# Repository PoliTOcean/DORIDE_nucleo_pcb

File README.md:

# NOME_REPO

> **Hai appena creato la repo da questo template? Fai questi passi, poi cancella questo riquadro.**
>
> 1. Rinomina la repo nel formato `<rov>_<componente>_pcb` (es. `nereo_power_pcb`).
> 2. Aggiungi il topic **`electronics`** (ingranaggio accanto ad "About"). I topic non vengono copiati dal template.
> 3. *Settings → Pages → Deploy from a branch → main → /docs → Save*.
> 4. Metti il progetto KiCad dentro `hardware/` (un solo `.kicad_pro`), con le librerie della scheda in `hardware/lib/local/`.
> 5. Sostituisci `NOME_REPO`, `NOME_PROGETTO` e il link al firmware qui sotto. `NOME_PROGETTO` è il nome del file `.kicad_pro` senza estensione.
> 6. Fai `git pull` prima di ogni modifica: dopo ogni push il bot aggiunge i render.

Descrizione della scheda (ROV, funzione, microcontrollore, numero di layer).
Firmware: [NOME_REPO_FIRMWARE](https://github.com/PoliTOcean/NOME_REPO_FIRMWARE)

| Top | Bottom |
|---|---|
|  |  |

## File di produzione

Gerber, forature e PDF dello schema si scaricano da **Actions → ultima run → pcb-outputs**.

## Struttura

~~~
hardware/            progetto KiCad
hardware/lib/local/  simboli, footprint e modelli 3D usati solo da questa scheda
docs/                render e interactive BOM (generati dal bot, non modificare)
~~~

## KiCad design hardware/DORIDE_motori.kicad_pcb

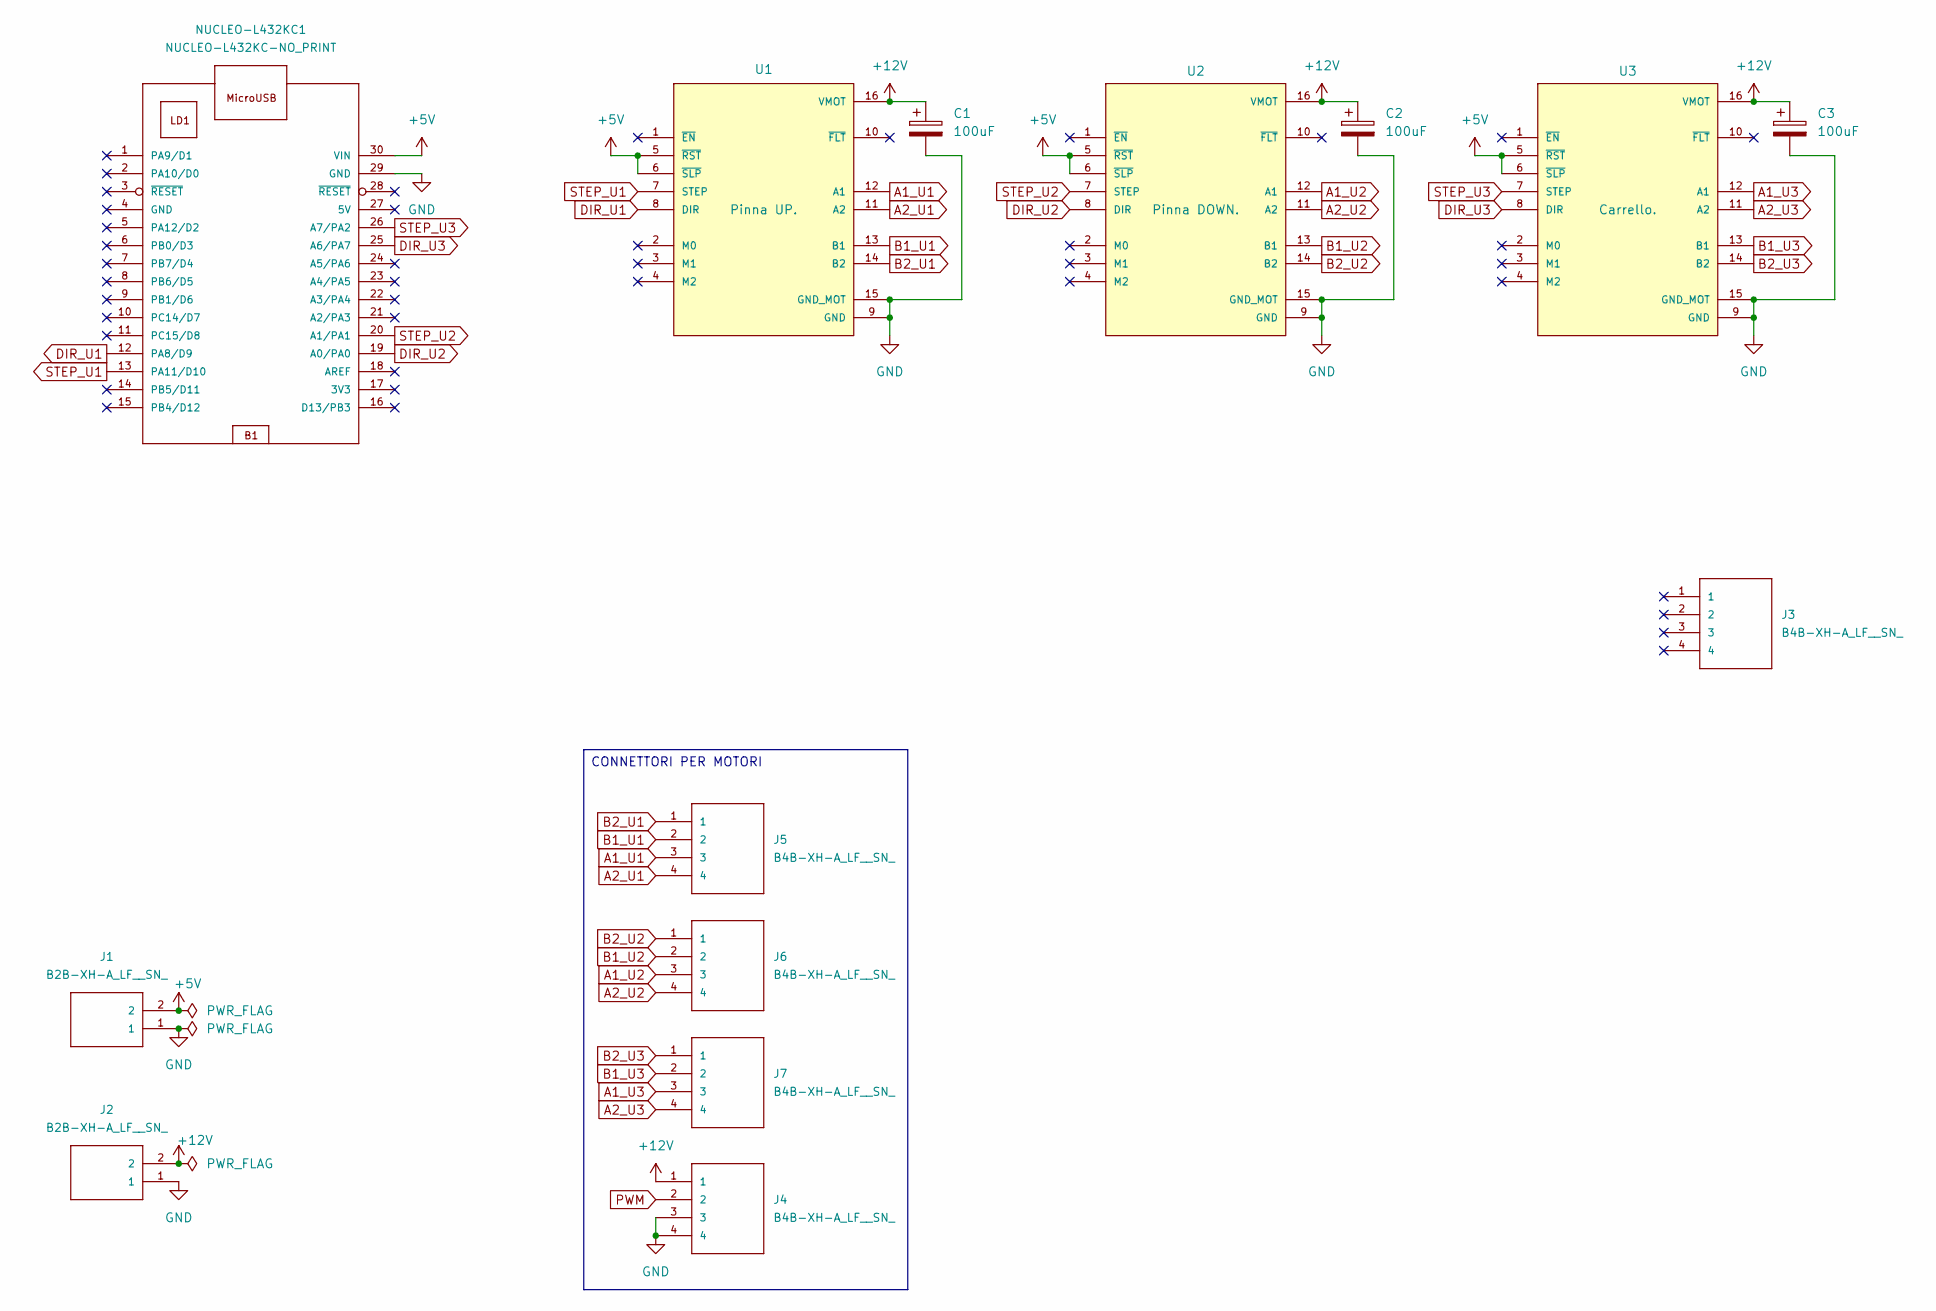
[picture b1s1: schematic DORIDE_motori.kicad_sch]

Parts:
C1, C2, C3: 100uF; CP_Elec_6.3x5.4
J1, J2: B2B-XH-A_LF__SN_; SHDR2W64P0X250_1X2_740X575X700
J3, J4, J5, J6, J7: B4B-XH-A_LF__SN_; SHDR4W64P0X250_1X4_1240X575X70
NUCLEO-L432KC1: NUCLEO-L432KC-NO_PRINT; NUCLEO-L432KC
U1, U2, U3: DRV8825_STEPPER_MOTOR_DRIVER_SMALL_BOARD; IC_DRV8825_STEPPER_MOTOR_DRIVER_CARRIER

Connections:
+5V: J1.2, NUCLEO-L432KC1.30 (VIN), U1.5 (~RST), U1.6 (~SLP), U2.5 (~RST), U2.6 (~SLP), U3.5 (~RST), U3.6 (~SLP)
+12V: C1.1, C2.1, C3.1, J2.2, J4.1, U1.16 (VMOT), U2.16 (VMOT), U3.16 (VMOT)
A1_U1: J5.3, U1.12 (A1)
A1_U2: J6.3, U2.12 (A1)
A1_U3: J7.3, U3.12 (A1)
A2_U1: J5.4, U1.11 (A2)
A2_U2: J6.4, U2.11 (A2)
A2_U3: J7.4, U3.11 (A2)
B1_U1: J5.2, U1.13 (B1)
B1_U2: J6.2, U2.13 (B1)
B1_U3: J7.2, U3.13 (B1)
B2_U1: J5.1, U1.14 (B2)
B2_U2: J6.1, U2.14 (B2)
B2_U3: J7.1, U3.14 (B2)
DIR_U1: NUCLEO-L432KC1.12 (PA8/D9), U1.8 (DIR)
DIR_U2: NUCLEO-L432KC1.19 (A0/PA0), U2.8 (DIR)
DIR_U3: NUCLEO-L432KC1.25 (A6/PA7), U3.8 (DIR)
GND: C1.2, C2.2, C3.2, J1.1, J2.1, J4.3, J4.4, NUCLEO-L432KC1.29 (GND), U1.9 (GND), U1.15 (GND_MOT), U2.9 (GND), U2.15 (GND_MOT), U3.9 (GND), U3.15 (GND_MOT)
PWM: J4.2
STEP_U1: NUCLEO-L432KC1.13 (PA11/D10), U1.7 (STEP)
STEP_U2: NUCLEO-L432KC1.20 (A1/PA1), U2.7 (STEP)
STEP_U3: NUCLEO-L432KC1.26 (A7/PA2), U3.7 (STEP)

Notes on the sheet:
CONNETTORI PER MOTORI

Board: 2 copper layers, 14 parts (0 on the bottom side), 21 nets, no tracks yet.
